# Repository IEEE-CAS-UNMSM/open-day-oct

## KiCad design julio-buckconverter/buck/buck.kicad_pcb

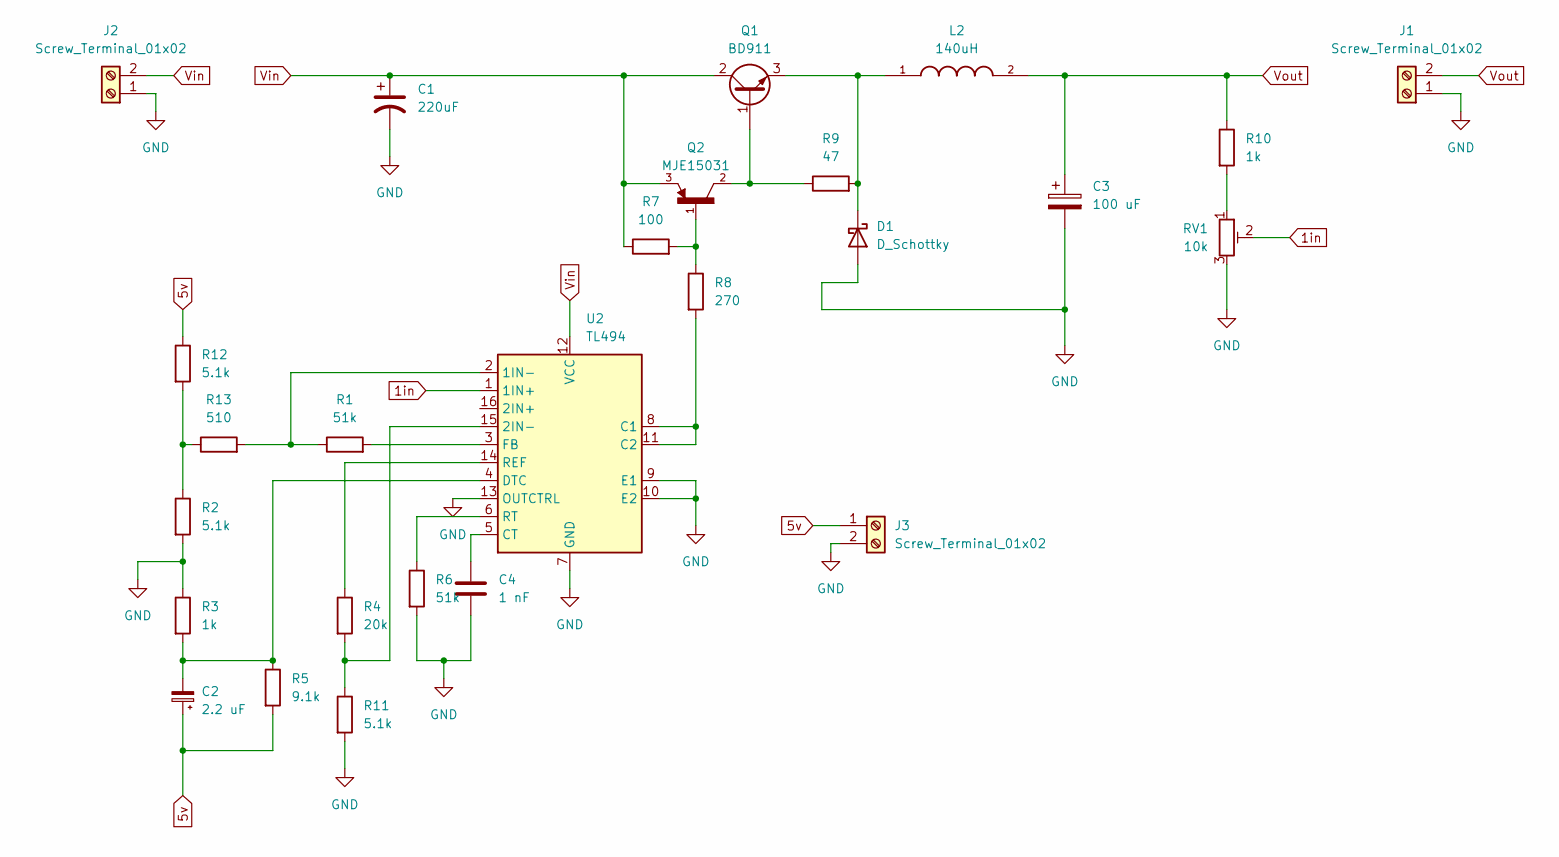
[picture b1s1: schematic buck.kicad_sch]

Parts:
C1: 220uF; CP_Axial_L10.0mm_D4.5mm_P15.00mm_Horizontal
C2: 2.2 uF; CP_Axial_L10.0mm_D4.5mm_P15.00mm_Horizontal
C3: 100 uF; CP_Axial_L10.0mm_D4.5mm_P15.00mm_Horizontal
C4: 1 nF; C_Axial_L3.8mm_D2.6mm_P7.50mm_Horizontal
D1: D_Schottky; D_A-405_P7.62mm_Horizontal
J1, J2, J3: Screw_Terminal_01x02; TerminalBlock_Wuerth_691311400102_P7.62mm
L2: 140uH; IND_HCTI-68-7.7; PARTREV N/A
Q1: BD911; TO-220-3_Vertical
Q2: MJE15031; TO254P1042X498X2993-3
R1: 51k; R_Axial_DIN0207_L6.3mm_D2.5mm_P7.62mm_Horizontal
R2, R12: 5.1k; R_Axial_DIN0207_L6.3mm_D2.5mm_P10.16mm_Horizontal
R3: 1k; R_Axial_DIN0207_L6.3mm_D2.5mm_P7.62mm_Horizontal
R4: 20k; R_Axial_DIN0207_L6.3mm_D2.5mm_P10.16mm_Horizontal
R5: 9.1k; R_Axial_DIN0207_L6.3mm_D2.5mm_P7.62mm_Horizontal
R6: 51k; R_Axial_DIN0207_L6.3mm_D2.5mm_P10.16mm_Horizontal
R7: 100; R_Axial_DIN0207_L6.3mm_D2.5mm_P7.62mm_Horizontal
R8: 270; R_Axial_DIN0207_L6.3mm_D2.5mm_P10.16mm_Horizontal
R9: 47; R_Axial_DIN0207_L6.3mm_D2.5mm_P7.62mm_Horizontal
R10: 1k; R_Axial_DIN0207_L6.3mm_D2.5mm_P10.16mm_Horizontal
R11: 5.1k; R_Axial_DIN0207_L6.3mm_D2.5mm_P7.62mm_Horizontal
R13: 510; R_Axial_DIN0207_L6.3mm_D2.5mm_P7.62mm_Horizontal
RV1: 10k; Potentiometer_ACP_CA9-V10_Vertical
U2: TL494; DIP-16_W7.62mm

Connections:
1in: RV1.2, U2.1 (1IN+)
5v: C2.1, J3.1, R5.2, R12.1
GND: C1.2, C3.2, C4.2, D1.2 (A), J1.1, J2.1, J3.2, R2.2, R3.1, R6.2, R11.2, RV1.3, U2.7 (GND), U2.9 (E1), U2.10 (E2), U2.13 (OUTCTRL)
unnamed: D1.1 (K), L2.1, Q1.3 (E), R9.2
unnamed: Q1.1 (B), Q2.2, R9.1
unnamed: Q2.1, R7.2, R8.1
unnamed: R10.2, RV1.1
unnamed: R2.1, R12.2, R13.1
unnamed: R1.1, R13.2, U2.2 (1IN-)
unnamed: R4.2, R11.1, U2.15 (2IN-)
unnamed: R8.2, U2.8 (C1), U2.11 (C2)
unnamed: C4.1, U2.5 (CT)
unnamed: C2.2, R3.2, R5.1, U2.4 (DTC)
unnamed: R1.2, U2.3 (FB)
unnamed: R4.1, U2.14 (REF)
unnamed: R6.1, U2.6 (RT)
Vin: C1.1, J2.2, Q1.2 (C), Q2.3, R7.1, U2.12 (VCC)
Vout: C3.1, J1.2, L2.2, R10.1

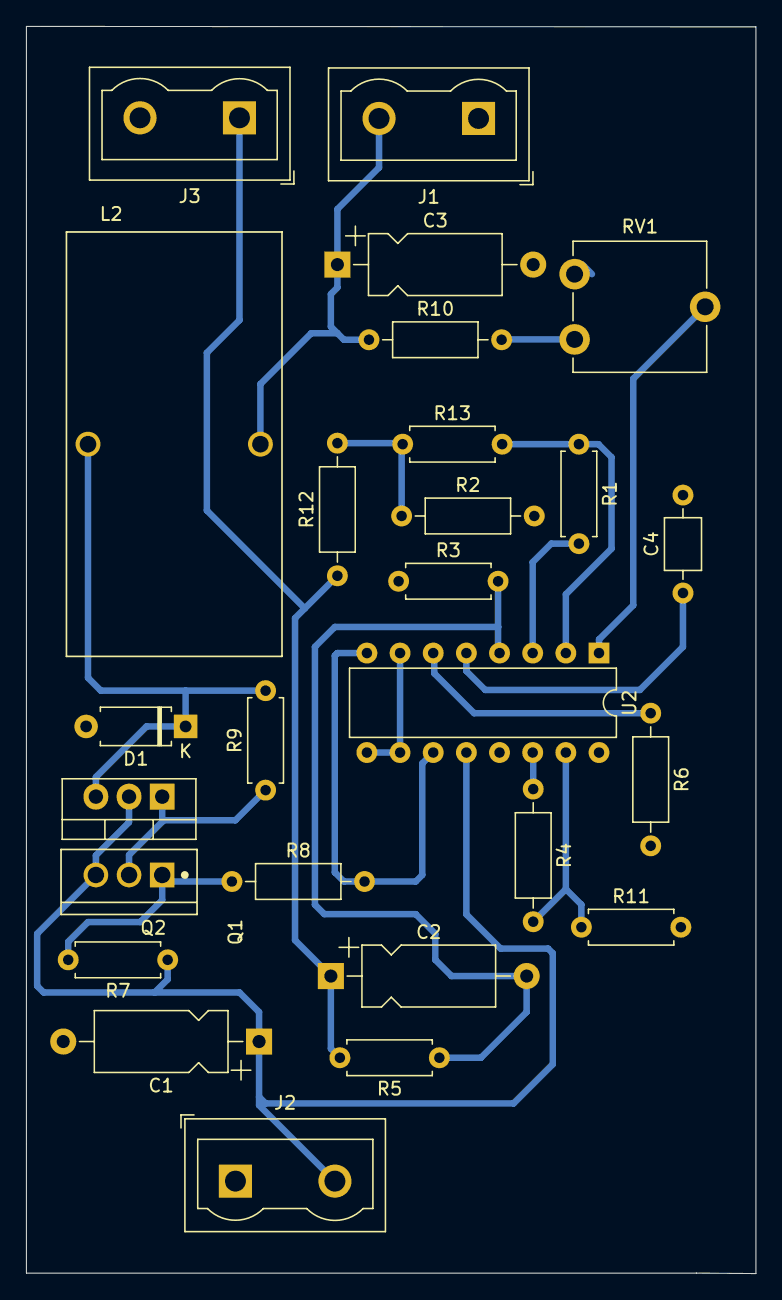
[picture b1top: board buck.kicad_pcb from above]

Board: 2 copper layers, 55.9 x 95.5 mm, 26 parts (0 on the bottom side), 18 nets.

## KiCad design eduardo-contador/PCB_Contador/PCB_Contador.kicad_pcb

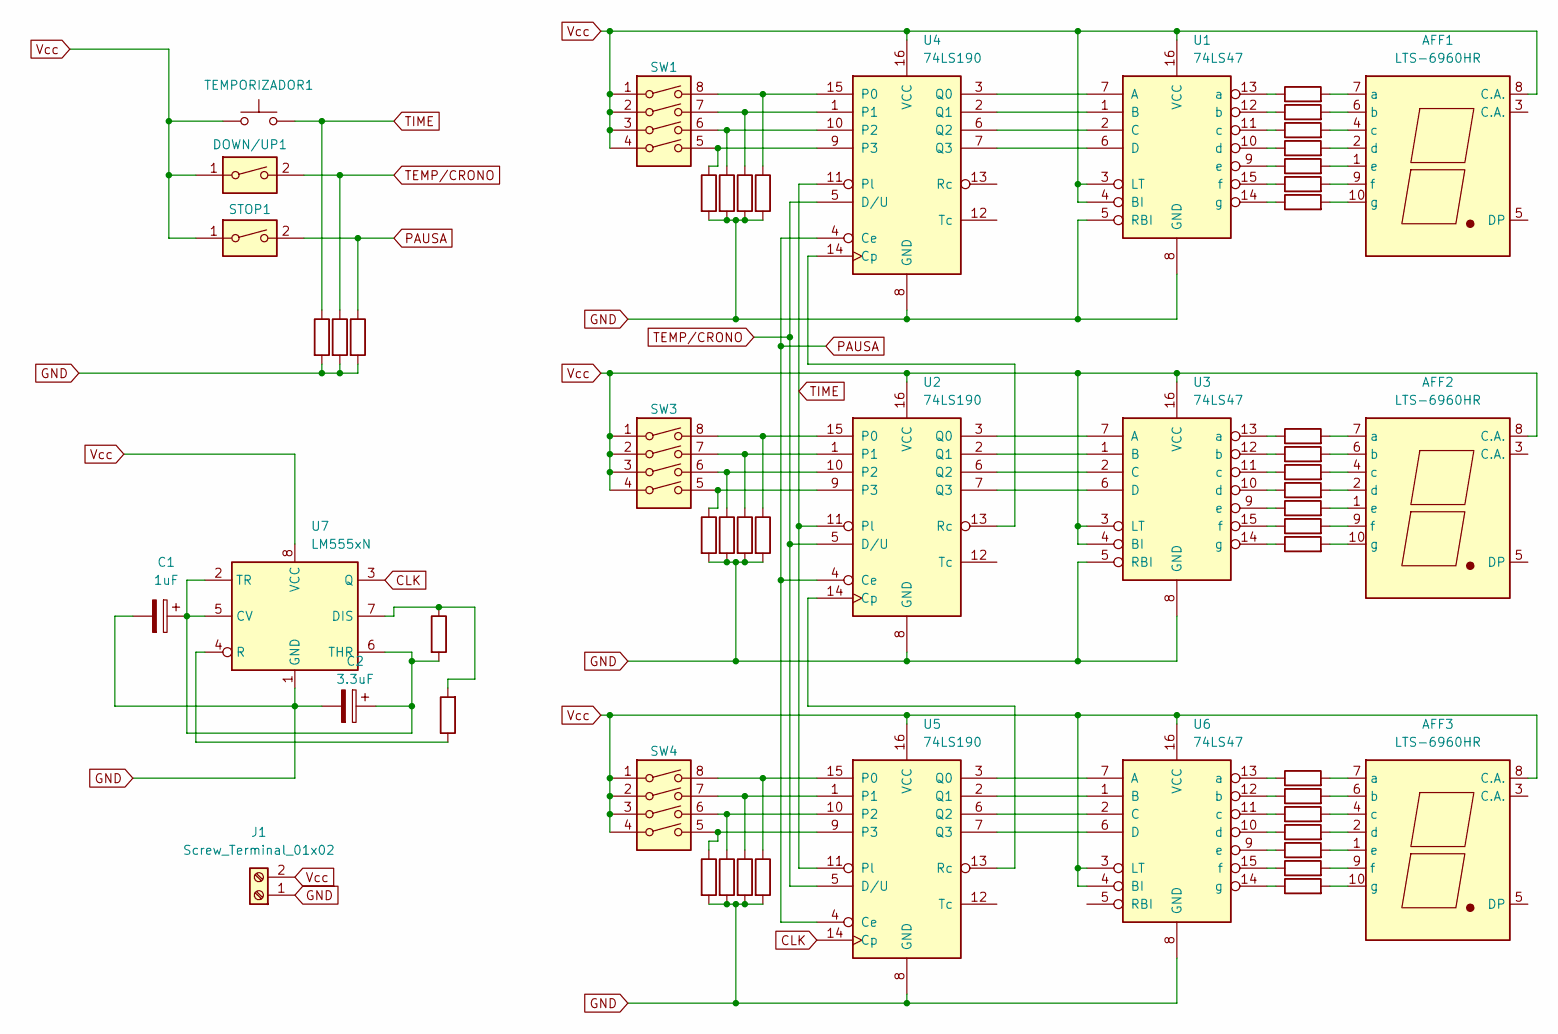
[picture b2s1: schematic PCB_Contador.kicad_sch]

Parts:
AFF1, AFF2, AFF3: LTS-6960HR; 7SegmentLED_LTS6760_LTS6780
C1: 1uF; CP_Radial_D5.0mm_P2.00mm
C2: 3.3uF; CP_Radial_D5.0mm_P2.00mm
DOWN/UP1: SW_DIP_SPSTx01_Slide_6.7x4.1mm_W7.62mm_P2.54mm_LowProfile
J1: Screw_Terminal_01x02; TerminalBlock_Xinya_XY308-2.54-2P_1x02_P2.54mm_Horizontal
R1, R2, R3, R4, R6, R7, R8, R9, R10, R11, R12, R13, R14, R15, R16, R17, R18, R19, R20, R21, R22, R23, R24, R25, R26, R27, R28, R29, R30, R31, R32, R33, R34, R35, R36: R; R_Axial_DIN0207_L6.3mm_D2.5mm_P10.16mm_Horizontal
R5: r=R; R_Axial_DIN0207_L6.3mm_D2.5mm_P10.16mm_Horizontal
R37: 200k; R_Axial_DIN0207_L6.3mm_D2.5mm_P10.16mm_Horizontal
R38: 36k; R_Axial_DIN0207_L6.3mm_D2.5mm_P10.16mm_Horizontal
STOP1: SW_DIP_SPSTx01_Slide_6.7x4.1mm_W7.62mm_P2.54mm_LowProfile
SW1, SW3, SW4: SW_DIP_x04; SW_DIP_SPSTx04_Slide_9.78x12.34mm_W7.62mm_P2.54mm
TEMPORIZADOR1: SW_Push; SW_PUSH_6mm
U1, U3, U6: 74LS47; DIP-16_W7.62mm
U2, U4, U5: 74LS190; DIP-16_W7.62mm
U7: LM555xN; DIP-8_W7.62mm

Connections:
CLK: U5.14 (Cp), U7.3 (Q)
GND: C1.2, C2.2, J1.1, R1.2, R2.2, R3.2, R4.2, R12.2, R13.2, R14.2, R15.2, R23.2, R24.2, R25.2, R26.2, R34.2, R35.2, R36.2, U1.5 (RBI), U1.8 (GND), U2.8 (GND), U3.5 (RBI), U3.8 (GND), U4.8 (GND), U5.8 (GND), U6.8 (GND), U7.1 (GND)
unnamed: AFF1.7 (a), R5.2
unnamed: AFF1.6 (b), R6.2
unnamed: AFF1.4 (c), R7.2
unnamed: AFF1.2 (d), R8.2
unnamed: AFF1.1 (e), R9.2
unnamed: AFF1.9 (f), R10.2
unnamed: AFF1.10 (g), R11.2
unnamed: AFF2.7 (a), R16.2
unnamed: AFF2.6 (b), R17.2
unnamed: AFF2.4 (c), R18.2
unnamed: AFF2.2 (d), R19.2
unnamed: AFF2.1 (e), R20.2
unnamed: AFF2.9 (f), R21.2
unnamed: AFF2.10 (g), R22.2
unnamed: AFF3.7 (a), R27.2
unnamed: AFF3.6 (b), R28.2
unnamed: AFF3.4 (c), R29.2
unnamed: AFF3.2 (d), R30.2
unnamed: AFF3.1 (e), R31.2
unnamed: AFF3.9 (f), R32.2
unnamed: AFF3.10 (g), R33.2
unnamed: U1.7 (A), U4.3 (Q0)
unnamed: U1.1 (B), U4.2 (Q1)
unnamed: U1.2 (C), U4.6 (Q2)
unnamed: U1.6 (D), U4.7 (Q3)
unnamed: R5.1, U1.13 (a)
unnamed: R6.1, U1.12 (b)
unnamed: R7.1, U1.11 (c)
unnamed: R8.1, U1.10 (d)
unnamed: R9.1, U1.9 (e)
unnamed: R10.1, U1.15 (f)
unnamed: R11.1, U1.14 (g)
unnamed: U2.14 (Cp), U5.13 (Rc)
unnamed: R15.1, SW3.8, U2.15 (P0)
unnamed: R14.1, SW3.7, U2.1
unnamed: R13.1, SW3.6, U2.10 (P2)
unnamed: R12.1, SW3.5, U2.9 (P3)
unnamed: U2.3 (Q0), U3.7 (A)
unnamed: U2.2 (Q1), U3.1 (B)
unnamed: U2.6 (Q2), U3.2 (C)
unnamed: U2.7 (Q3), U3.6 (D)
unnamed: U2.13 (Rc), U4.14 (Cp)
unnamed: R16.1, U3.13 (a)
unnamed: R17.1, U3.12 (b)
unnamed: R18.1, U3.11 (c)
unnamed: R19.1, U3.10 (d)
unnamed: R20.1, U3.9 (e)
unnamed: R21.1, U3.15 (f)
unnamed: R22.1, U3.14 (g)
unnamed: R4.1, SW1.8, U4.15 (P0)
unnamed: R3.1, SW1.7, U4.1
unnamed: R2.1, SW1.6, U4.10 (P2)
unnamed: R1.1, SW1.5, U4.9 (P3)
unnamed: R26.1, SW4.8, U5.15 (P0)
unnamed: R25.1, SW4.7, U5.1
unnamed: R24.1, SW4.6, U5.10 (P2)
unnamed: R23.1, SW4.5, U5.9 (P3)
unnamed: U5.3 (Q0), U6.7 (A)
unnamed: U5.2 (Q1), U6.1 (B)
unnamed: U5.6 (Q2), U6.2 (C)
unnamed: U5.7 (Q3), U6.6 (D)
unnamed: R27.1, U6.13 (a)
unnamed: R28.1, U6.12 (b)
unnamed: R29.1, U6.11 (c)
unnamed: R30.1, U6.10 (d)
unnamed: R31.1, U6.9 (e)
unnamed: R32.1, U6.15 (f)
unnamed: R33.1, U6.14 (g)
unnamed: C1.1, C2.1, R37.2, U7.2 (TR), U7.5 (CV), U7.6 (THR)
unnamed: R37.1, R38.2, U7.7 (DIS)
unnamed: R38.1, U7.4 (R)
PAUSA: R36.1, STOP1.2, U2.4 (Ce), U4.4 (Ce), U5.4 (Ce)
TEMP/CRONO: DOWN/UP1.2, R35.1, U2.5 (D/U), U4.5 (D/U), U5.5 (D/U)
TIME: R34.1, TEMPORIZADOR1.2, U2.11 (Pl), U4.11 (Pl), U5.11 (Pl)
Vcc: AFF1.8 (C.A.), AFF2.8 (C.A.), AFF3.8 (C.A.), DOWN/UP1.1, J1.2, STOP1.1, SW1.1, SW1.2, SW1.3, SW1.4, SW3.1, SW3.2, SW3.3, SW3.4, SW4.1, SW4.2, SW4.3, SW4.4, TEMPORIZADOR1.1, U1.3 (LT), U1.4 (BI), U1.16 (VCC), U2.16 (VCC), U3.3 (LT), U3.4 (BI), U3.16 (VCC), U4.16 (VCC), U5.16 (VCC), U6.3 (LT), U6.4 (BI), U6.16 (VCC), U7.8 (VCC)

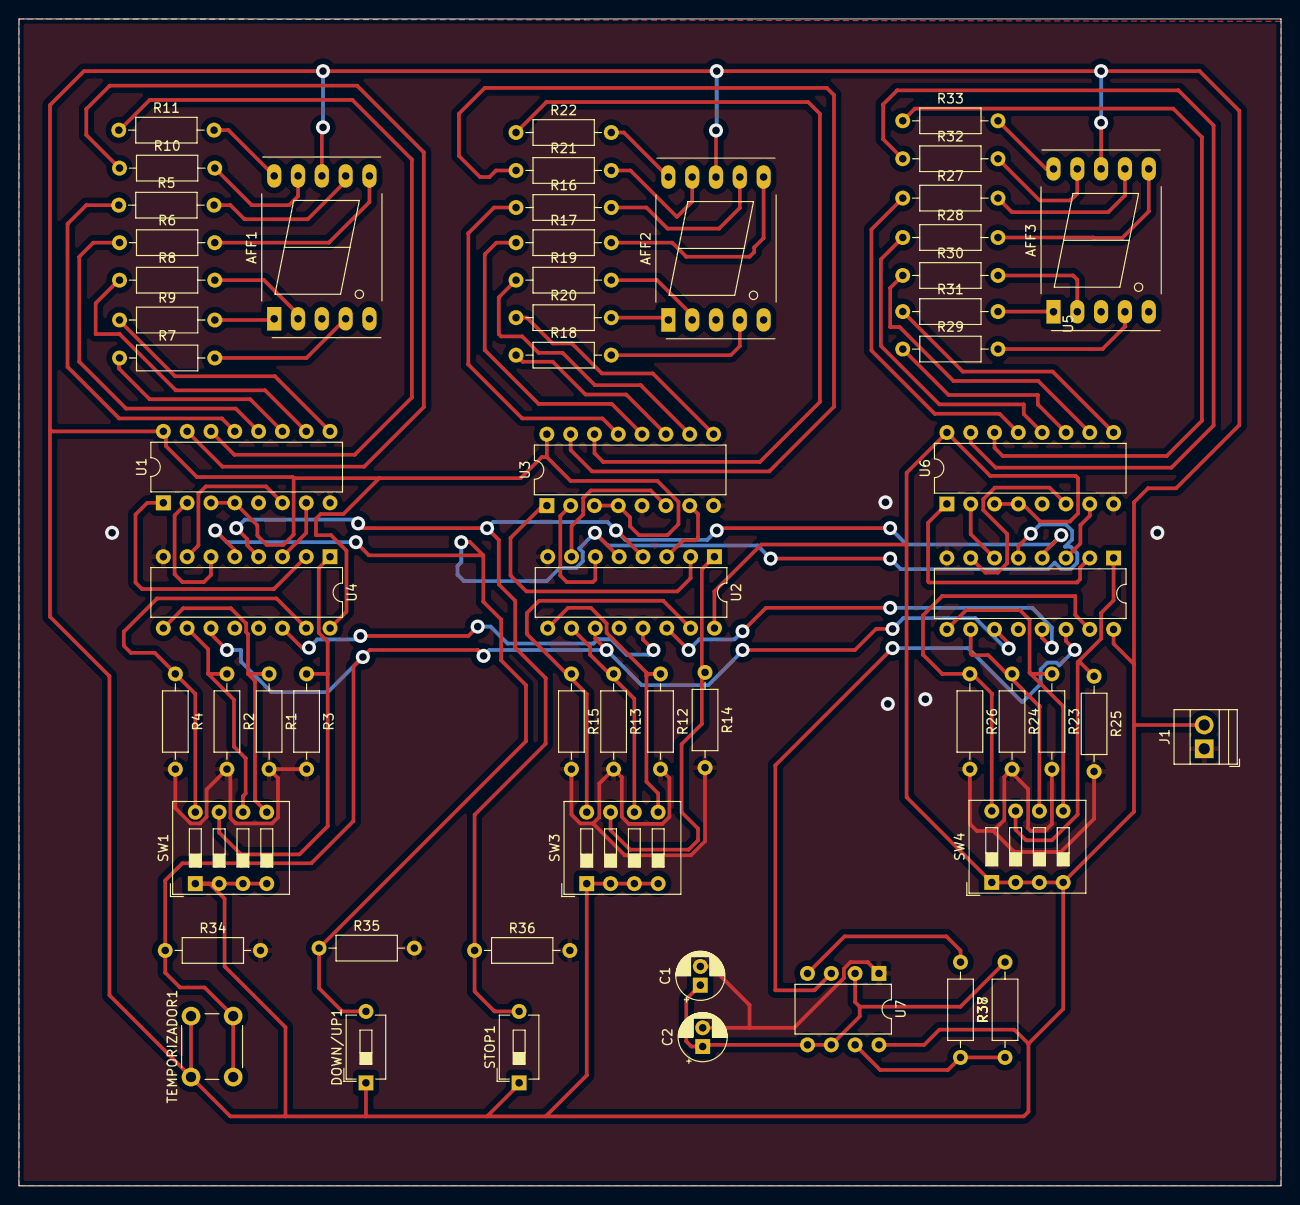
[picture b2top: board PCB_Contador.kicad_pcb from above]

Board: 2 copper layers, 134.6 x 124.5 mm, 57 parts (0 on the bottom side), 77 nets.

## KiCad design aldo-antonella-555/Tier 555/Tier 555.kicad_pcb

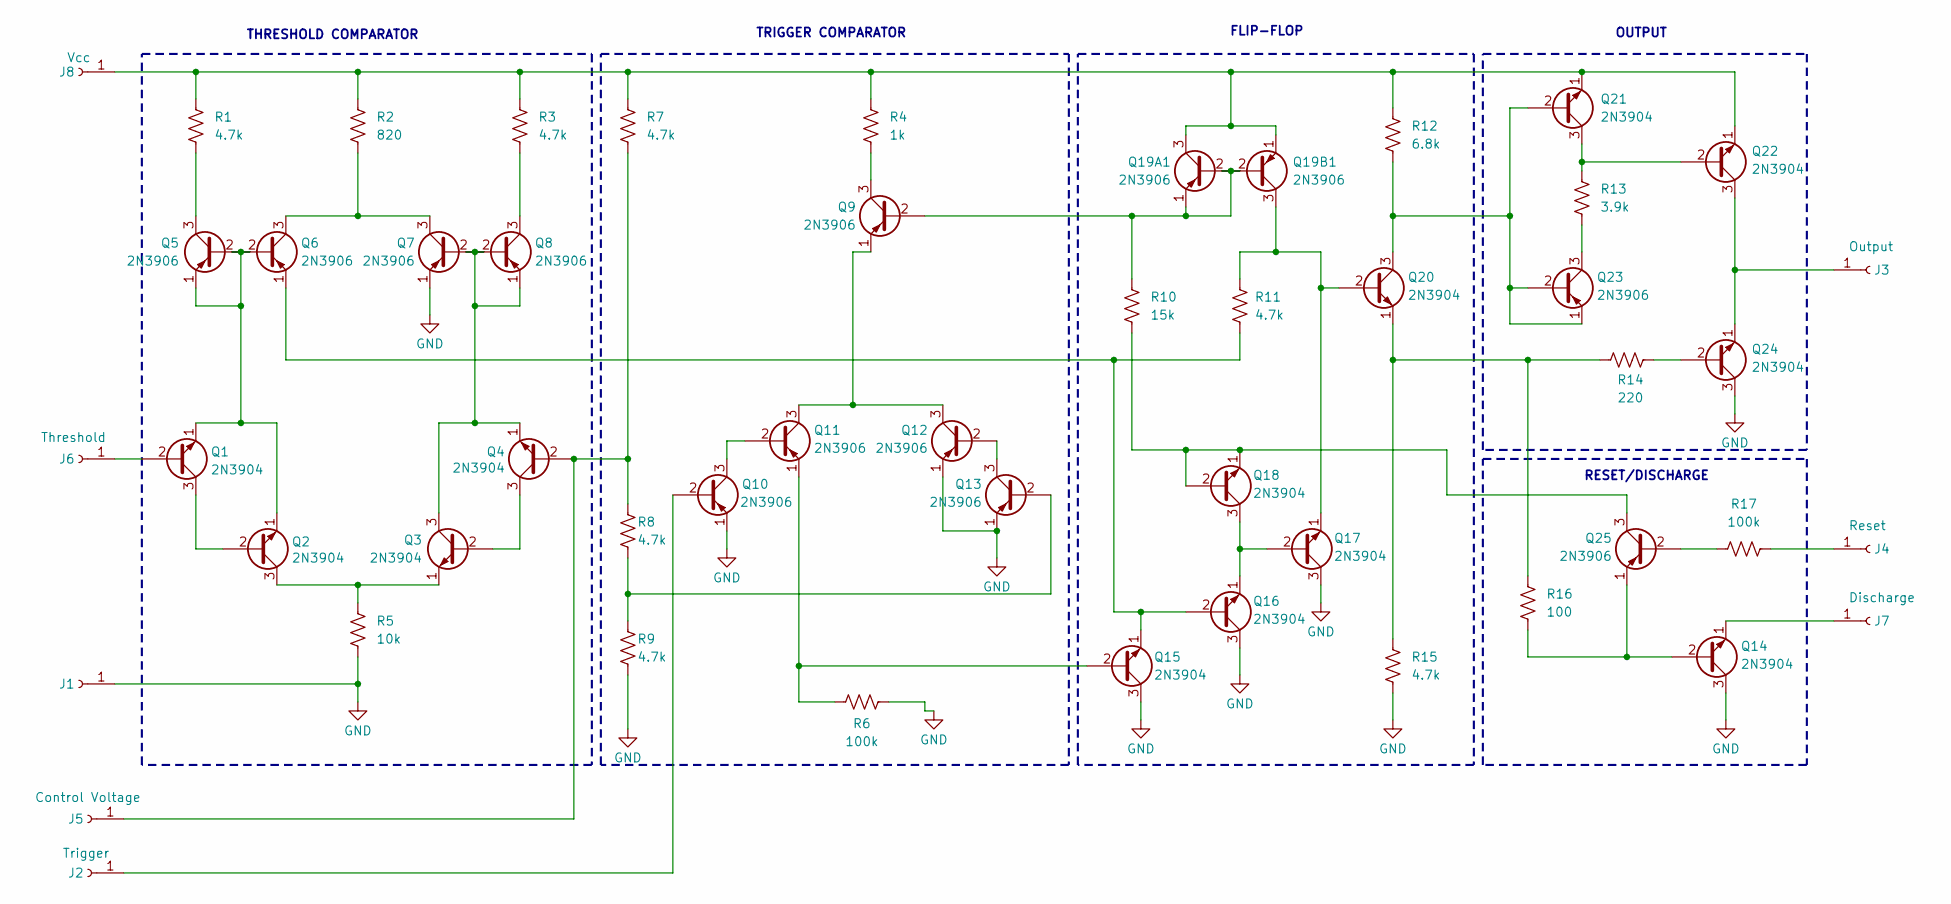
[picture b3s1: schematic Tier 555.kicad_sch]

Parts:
J1: GND; PinHeader_1x01_P2.54mm_Vertical
J2: Trigger; PinHeader_1x01_P2.54mm_Vertical
J3: Output; PinHeader_1x01_P2.54mm_Vertical
J4: Reset; PinHeader_1x01_P2.54mm_Vertical
J5: Control Voltage; PinHeader_1x01_P2.54mm_Vertical
J6: Threshold; PinHeader_1x01_P2.54mm_Vertical
J7: Discharge; PinHeader_1x01_P2.54mm_Vertical
J8: Vcc; PinHeader_1x01_P2.54mm_Vertical
Q1, Q2, Q3, Q4, Q14, Q15, Q16, Q17, Q18, Q20, Q21, Q22, Q24: 2N3904; TO-92_Inline
Q5, Q6, Q7, Q8, Q9, Q10, Q11, Q12, Q13, Q19A1, Q19B1, Q23, Q25: 2N3906; TO-92_Inline
R1, R3, R7, R8, R9, R11, R15: 4.7k; R_Axial_DIN0207_L6.3mm_D2.5mm_P10.16mm_Horizontal
R2: 820; R_Axial_DIN0207_L6.3mm_D2.5mm_P10.16mm_Horizontal
R4: 1k; R_Axial_DIN0207_L6.3mm_D2.5mm_P10.16mm_Horizontal
R5: 10k; R_Axial_DIN0207_L6.3mm_D2.5mm_P10.16mm_Horizontal
R6, R17: 100k; R_Axial_DIN0207_L6.3mm_D2.5mm_P10.16mm_Horizontal
R10: 15k; R_Axial_DIN0207_L6.3mm_D2.5mm_P10.16mm_Horizontal
R12: 6.8k; R_Axial_DIN0207_L6.3mm_D2.5mm_P10.16mm_Horizontal
R13: 3.9k; R_Axial_DIN0207_L6.3mm_D2.5mm_P10.16mm_Horizontal
R14: 220; R_Axial_DIN0207_L6.3mm_D2.5mm_P10.16mm_Horizontal
R16: 100; R_Axial_DIN0207_L6.3mm_D2.5mm_P10.16mm_Horizontal

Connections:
GND: J1.1, Q7.1 (E), Q10.1 (E), Q12.1 (E), Q13.1 (E), Q14.3 (C), Q15.3 (C), Q16.3 (C), Q17.3 (C), Q24.3 (C), R5.2, R6.1, R9.2, R15.2
unnamed: J2.1, Q10.2 (B)
unnamed: J3.1, Q22.3 (C), Q24.1 (E)
unnamed: J4.1, R17.2
unnamed: J5.1, Q4.2 (B), R7.2, R8.1
unnamed: J6.1, Q1.2 (B)
unnamed: J7.1, Q14.1 (E)
unnamed: J8.1, Q19A1.3 (C), Q19B1.1 (E), Q21.1 (E), Q22.1 (E), R1.1, R2.1, R3.1, R4.1, R7.1, R12.1
unnamed: Q1.3 (C), Q2.2 (B)
unnamed: Q1.1 (E), Q2.1 (E), Q5.1 (E), Q5.2 (B), Q6.2 (B)
unnamed: Q2.3 (C), Q3.1 (E), R5.1
unnamed: Q3.2 (B), Q4.3 (C)
unnamed: Q3.3 (C), Q4.1 (E), Q7.2 (B), Q8.1 (E), Q8.2 (B)
unnamed: Q5.3 (C), R1.2
unnamed: Q6.3 (C), Q7.3 (C), R2.2
unnamed: Q8.3 (C), R3.2
unnamed: Q9.3 (C), R4.2
unnamed: Q10.3 (C), Q11.2 (B)
unnamed: Q9.1 (E), Q11.3 (C), Q12.3 (C)
unnamed: Q11.1 (E), Q15.2 (B), R6.2
unnamed: Q12.2 (B), Q13.3 (C)
unnamed: Q13.2 (B), R8.2, R9.1
unnamed: Q14.2 (B), Q25.1 (E), R16.2
unnamed: Q6.1 (E), Q15.1 (E), Q16.2 (B), R11.2
unnamed: Q16.1 (E), Q17.2 (B), Q18.3 (C)
unnamed: Q17.1 (E), Q19B1.3 (C), Q20.2 (B), R11.1
unnamed: Q18.1 (E), Q18.2 (B), Q25.3 (C), R10.2
unnamed: Q9.2 (B), Q19A1.1 (E), Q19A1.2 (B), Q19B1.2 (B), R10.1
unnamed: Q20.3 (C), Q21.2 (B), Q23.1 (E), Q23.2 (B), R12.2
unnamed: Q20.1 (E), R14.1, R15.1, R16.1
unnamed: Q21.3 (C), Q22.2 (B), R13.1
unnamed: Q23.3 (C), R13.2
unnamed: Q24.2 (B), R14.2
unnamed: Q25.2 (B), R17.1

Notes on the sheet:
OUTPUT
RESET/DISCHARGE
FLIP-FLOP
THRESHOLD COMPARATOR
TRIGGER COMPARATOR

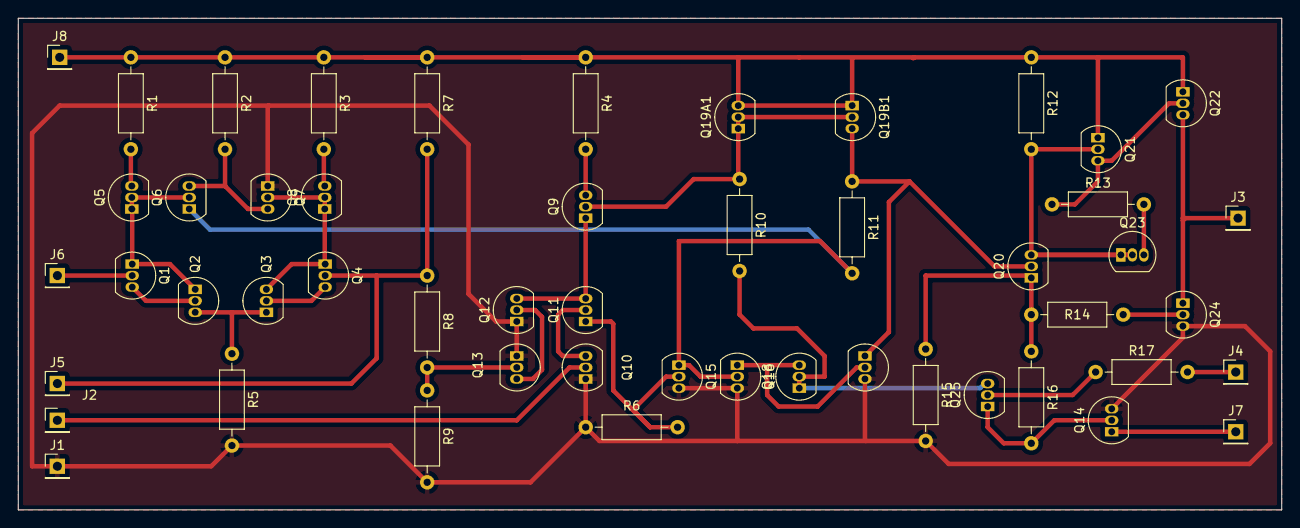
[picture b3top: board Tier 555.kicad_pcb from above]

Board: 2 copper layers, 139.7 x 54.4 mm, 51 parts (0 on the bottom side), 34 nets.

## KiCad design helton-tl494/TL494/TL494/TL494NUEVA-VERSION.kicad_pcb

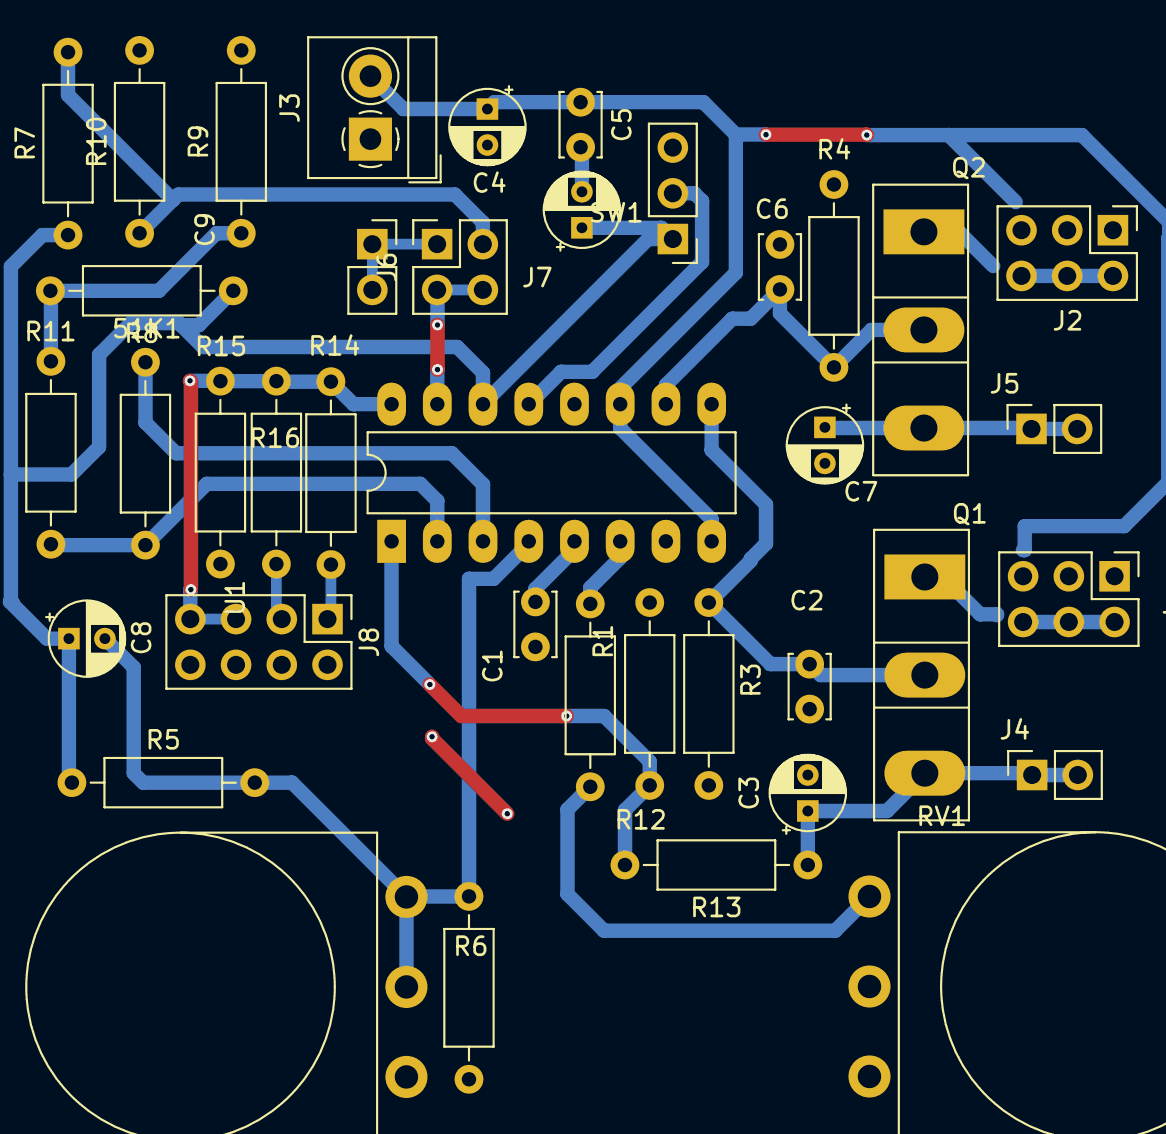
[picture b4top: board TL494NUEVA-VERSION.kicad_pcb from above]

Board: 2 copper layers, 39 parts (0 on the bottom side), 22 nets.

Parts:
51K1: 510; R_Axial_DIN0207_L6.3mm_D2.5mm_P10.16mm_Horizontal
C1: 1uF; C_Disc_D3.4mm_W2.1mm_P2.50mm
C2, C6: 15pF; C_Disc_D3.4mm_W2.1mm_P2.50mm
C3, C7: 10uF; CP_Radial_D4.0mm_P2.00mm
C4, C8, C9: 100uF; CP_Radial_D4.0mm_P2.00mm
C5: 10nF; C_Disc_D3.4mm_W2.1mm_P2.50mm
J1, J2: Jumper E1; PinHeader_2x03_P2.54mm_Vertical
J3: +-; TerminalBlock_4Ucon_1x02_P3.50mm_Horizontal
J4, J5, J7: Vout1; PinSocket_1x02_P2.54mm_Vertical
J6: Conn_02x02_Odd_Even; PinSocket_2x02_P2.54mm_Vertical
J8: Conn_02x04_Odd_Even; PinHeader_2x04_P2.54mm_Vertical
Q1, Q2: NMOS; TO-247-3_Vertical
R1: 2k; R_Axial_DIN0207_L6.3mm_D2.5mm_P10.16mm_Horizontal
R3, R4: 68; R_Axial_DIN0207_L6.3mm_D2.5mm_P10.16mm_Horizontal
R5: 100k; R_Axial_DIN0207_L6.3mm_D2.5mm_P10.16mm_Horizontal
R6, R10: 1k; R_Axial_DIN0207_L6.3mm_D2.5mm_P10.16mm_Horizontal
R7: 4k; R_Axial_DIN0207_L6.3mm_D2.5mm_P10.16mm_Horizontal
R8, R9: 5.1k; R_Axial_DIN0207_L6.3mm_D2.5mm_P10.16mm_Horizontal
R11: 510; R_Axial_DIN0207_L6.3mm_D2.5mm_P10.16mm_Horizontal
R12, R14, R15: 10k; R_Axial_DIN0207_L6.3mm_D2.5mm_P10.16mm_Horizontal
R13: 50k; R_Axial_DIN0207_L6.3mm_D2.5mm_P10.16mm_Horizontal
R16: 30k; R_Axial_DIN0207_L6.3mm_D2.5mm_P10.16mm_Horizontal
RV1: 20k; Potentiometer_Omeg_PC16BU_Vertical
RV2: 100k; Potentiometer_Omeg_PC16BU_Vertical
SW1: CTRL; PinHeader_1x03_P2.54mm_Vertical
U1: TL494; DIP-16_W7.62mm_LongPads

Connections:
1IN+: R12.1, R13.2, U1.1 (1IN+)
1IN-: 51K1.1, R11.1, U1.2 (1IN-)
2IN+: J8.5, J8.7, R14.1, R15.2, R16.2, U1.16 (2IN+)
2IN-: J6.2, J6.4, U1.15 (2IN-)
CT: C1.1, U1.5 (CT)
CTRL: SW1.2 (B), U1.13 (OUTCTRL)
DTC: C8.2, R5.2, R6.2, RV2.1, RV2.2, U1.4 (DTC)
E1: C2.2, Q1.2 (G), R3.1, U1.9 (E1)
E2: C6.2, Q2.2 (G), R4.1, U1.10 (E2)
FB: 51K1.2, U1.3 (FB)
GNDREF: C1.2, C2.1, C3.2, C4.2, C5.2, C6.1, C7.2, C9.2, J3.1, J8.8, R3.2, R4.2, R6.1, R9.2, R10.2, R12.2, R15.1, RV1.1, RV1.2, RV2.3, SW1.3 (C), U1.7 (GND)
unnamed: C7.1, J5.1, J5.2, Q2.3 (S)
unnamed: J6.1, J7.1, J7.2
unnamed: J6.3, R7.2, R10.1
unnamed: J8.1, R14.2
unnamed: J8.3, R16.1
unnamed: R1.2, RV1.3
unnamed: R8.2, R9.1, R11.2
OUTV1: C3.1, J4.1, J4.2, Q1.3 (S), R13.1
RT: R1.1, U1.6 (RT)
VCC: C4.1, C5.1, J3.2, U1.8 (C1), U1.11 (C2), U1.12 (VCC)
VREF: C8.1, C9.1, R5.1, R7.1, R8.1, SW1.1 (A), U1.14 (REF)

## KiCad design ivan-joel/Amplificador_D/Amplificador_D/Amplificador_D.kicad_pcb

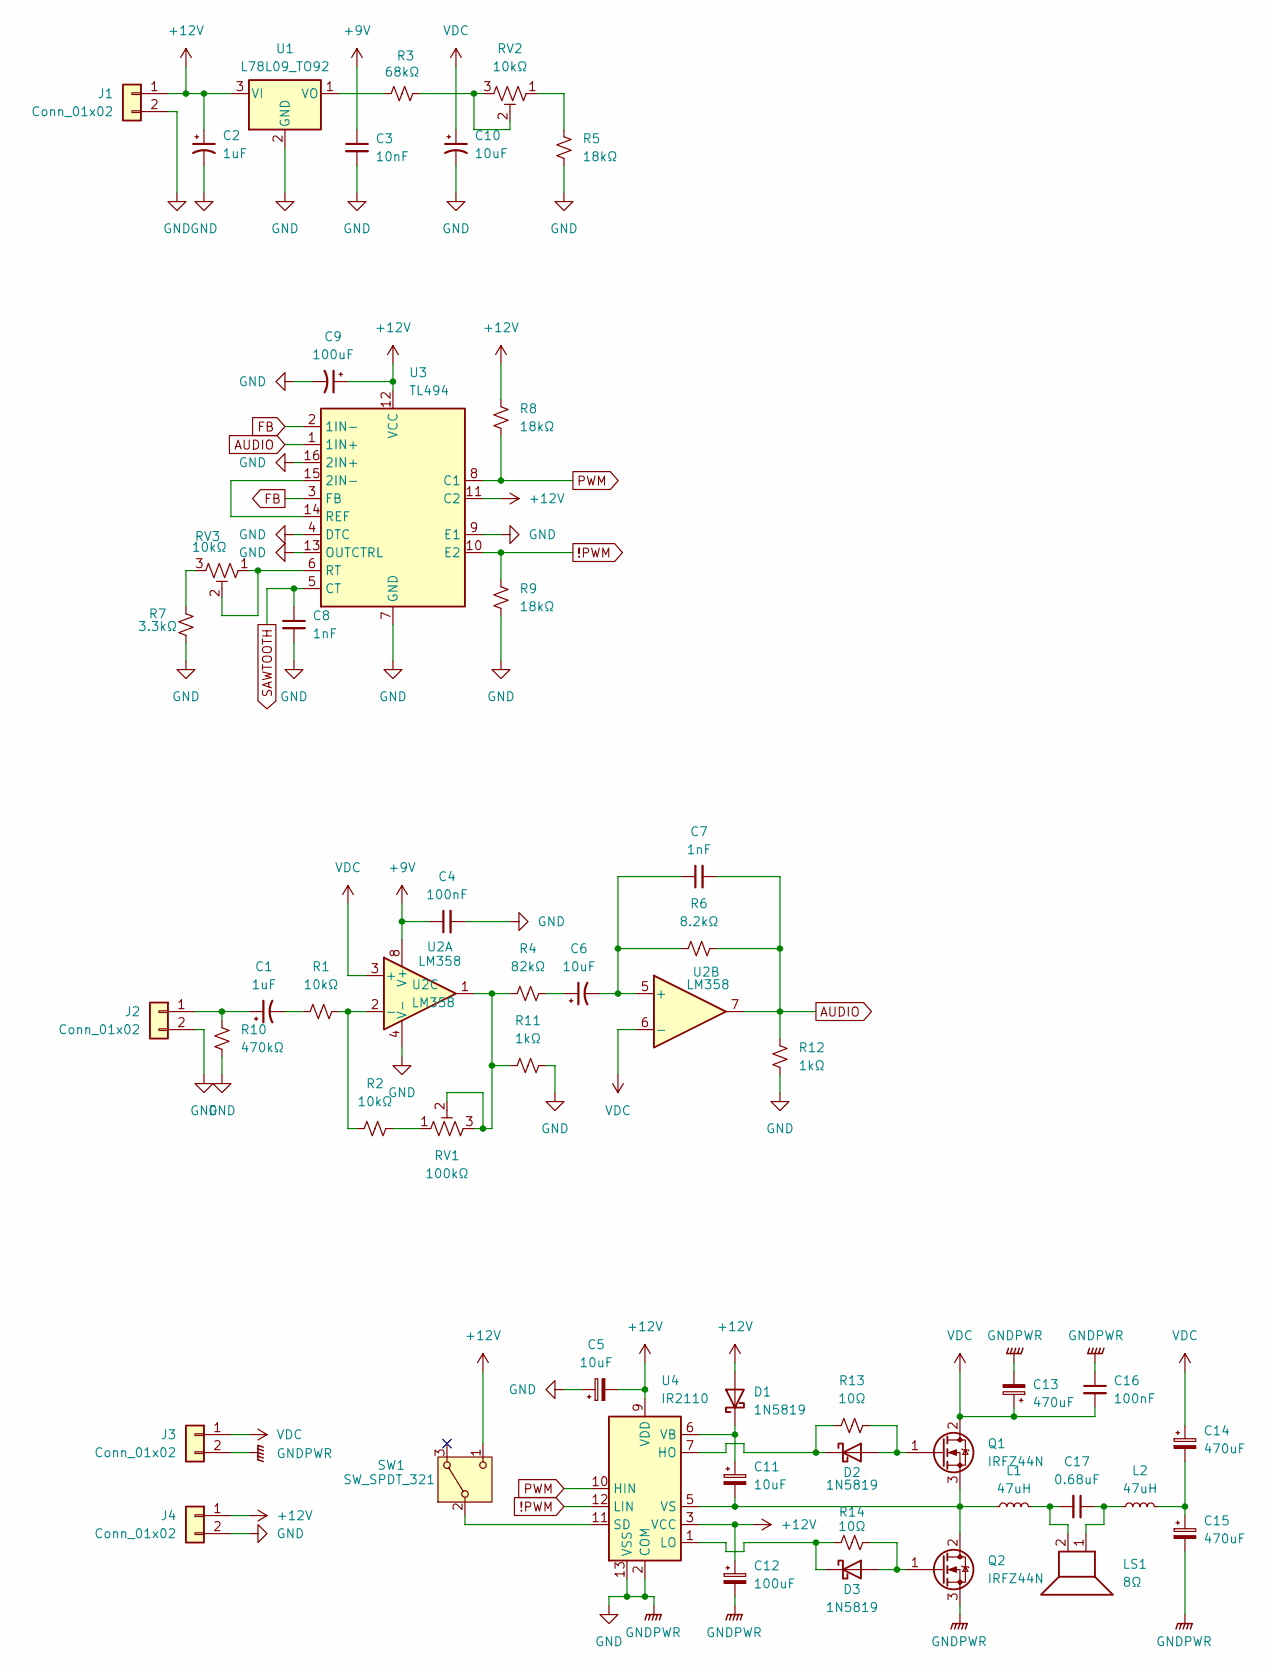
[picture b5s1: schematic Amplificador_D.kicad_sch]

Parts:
C1, C2: 1uF; CP_Radial_D5.0mm_P2.00mm
C3: 10nF; C_Disc_D3.8mm_W2.6mm_P2.50mm
C4: 100nF; C_Disc_D5.0mm_W2.5mm_P5.00mm
C5, C6, C10, C11: 10uF; CP_Radial_D5.0mm_P2.00mm
C7, C8: 1nF; C_Disc_D3.8mm_W2.6mm_P2.50mm
C9: 100uF; CP_Radial_D6.3mm_P2.50mm
C12: 100uF; CP_Radial_D8.0mm_P2.50mm
C13, C14, C15: 470uF; CP_Radial_D10.0mm_P5.00mm
C16: 100nF; C_Disc_D3.8mm_W2.6mm_P2.50mm
C17: 0.68uF; C_Rect_L7.0mm_W3.5mm_P5.00mm
D1, D2, D3: 1N5819; D_DO-41_SOD81_P10.16mm_Horizontal
J1: Conn_01x02; BarrelJack_GCT_DCJ200-10-A_Horizontal
J2, J3, J4: Conn_01x02; JST_XH_B2B-XH-A_1x02_P2.50mm_Vertical
L1, L2: 47uH; L_Radial_D12.5mm_P7.00mm_Fastron_09HCP
LS1: 8Ω; Molex_KK-396_A-41791-0002_1x02_P3.96mm_Vertical
Q1, Q2: IRFZ44N; TO-220-3_Vertical
R1, R2: 10kΩ; R_Axial_DIN0204_L3.6mm_D1.6mm_P7.62mm_Horizontal
R3: 68kΩ; R_Axial_DIN0204_L3.6mm_D1.6mm_P7.62mm_Horizontal
R4: 82kΩ; R_Axial_DIN0204_L3.6mm_D1.6mm_P7.62mm_Horizontal
R5, R8, R9: 18kΩ; R_Axial_DIN0204_L3.6mm_D1.6mm_P7.62mm_Horizontal
R6: 8.2kΩ; R_Axial_DIN0204_L3.6mm_D1.6mm_P7.62mm_Horizontal
R7: 3.3kΩ; R_Axial_DIN0204_L3.6mm_D1.6mm_P7.62mm_Horizontal
R10: 470kΩ; R_Axial_DIN0204_L3.6mm_D1.6mm_P7.62mm_Horizontal
R11, R12: 1kΩ; R_Axial_DIN0204_L3.6mm_D1.6mm_P7.62mm_Horizontal
R13, R14: 10Ω; R_Axial_DIN0204_L3.6mm_D1.6mm_P7.62mm_Horizontal
RV1: 100kΩ; Potentiometer_Bourns_3296W_Vertical
RV2, RV3: 10kΩ; Potentiometer_Bourns_3296W_Vertical
SW1: SW_SPDT_321; SW_NKK_GW12LJP
U1: L78L09_TO92; TO-92_Inline_Wide
U2: LM358; DIP-8_W7.62mm
U3: TL494; DIP-16_W7.62mm
U4: IR2110; DIP-14_W7.62mm

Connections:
!PWM: R9.1, U3.10 (E2), U4.12 (LIN)
+9V: C3.1, C4.1, U2.8 (V+)
+12V: C2.1, C5.2, C9.1, C12.1, D1.2 (A), J1.1, J4.1, R8.1, SW1.1 (C), U1.3 (VI), U3.11 (C2), U3.12 (VCC), U4.3 (VCC), U4.9 (VDD)
AUDIO: C7.2, R6.2, R12.2, U2.7, U3.1 (1IN+)
FB: U3.2 (1IN-), U3.3 (FB)
GND: C2.2, C3.2, C4.2, C5.1, C8.2, C9.2, C10.2, C12.2, C13.2, C15.2, C16.1, J1.2, J2.2, J3.2, J4.2, Q2.3 (S), R5.2, R7.2, R9.2, R10.2, R11.2, R12.1, U1.2 (GND), U2.4 (V-), U3.4 (DTC), U3.7 (GND), U3.9 (E1), U3.13 (OUTCTRL), U3.16 (2IN+), U4.2 (COM), U4.13 (VSS)
unnamed: C1.2, R1.1
unnamed: C6.1, R4.2
unnamed: C14.2, C15.1, L2.2
unnamed: C17.1, L2.1, LS1.1
unnamed: C17.2, L1.2, LS1.2
unnamed: C11.1, D1.1 (K), U4.6 (VB)
unnamed: D2.2 (A), Q1.1 (G), R13.2
unnamed: D2.1 (K), R13.1, U4.7 (HO)
unnamed: D3.2 (A), Q2.1 (G), R14.2
unnamed: D3.1 (K), R14.1, U4.1 (LO)
unnamed: C1.1, J2.1, R10.1
unnamed: C11.2, L1.1, Q1.3 (S), Q2.2 (D), U4.5 (VS)
unnamed: R2.2, RV1.1
unnamed: R3.2, RV2.2, RV2.3
unnamed: R5.1, RV2.1
unnamed: R7.1, RV3.3
unnamed: R4.1, R11.1, RV1.2, RV1.3, U2.1
unnamed: SW1.2 (B), U4.11 (SD)
unnamed: R3.1, U1.1 (VO)
unnamed: R1.2, R2.1, U2.2 (-)
unnamed: C6.2, C7.1, R6.1, U2.5 (+)
unnamed: U3.14 (REF), U3.15 (2IN-)
unnamed: RV3.1, RV3.2, U3.6 (RT)
PWM: R8.2, U3.8 (C1), U4.10 (HIN)
SAWTOOTH: C8.1, U3.5 (CT)
VDC: C10.1, C13.1, C14.1, C16.2, J3.1, Q1.2 (D), U2.3 (+), U2.6 (-)

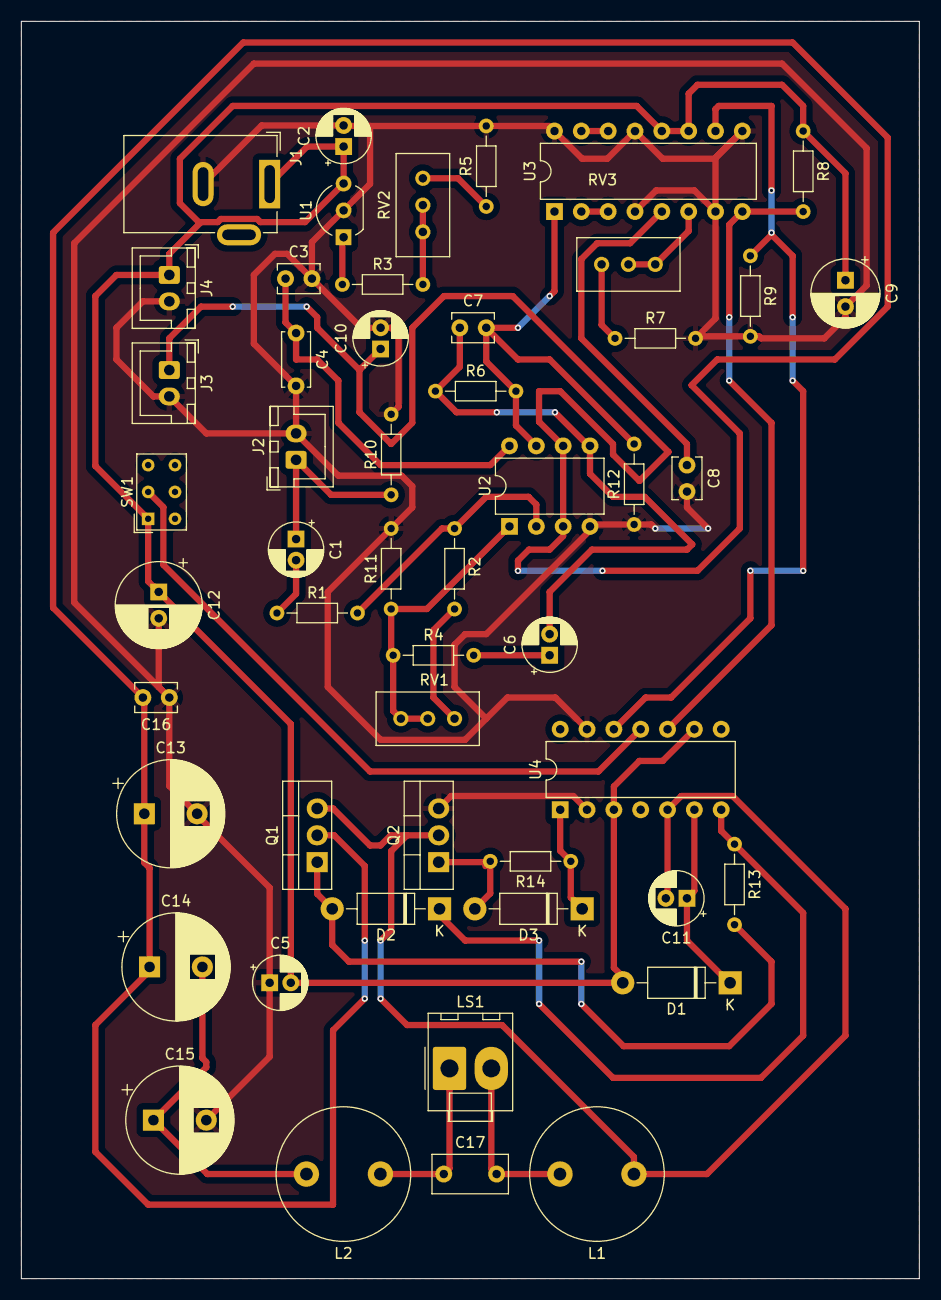
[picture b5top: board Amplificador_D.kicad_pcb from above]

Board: 2 copper layers, 85.0 x 119.0 mm, 51 parts (0 on the bottom side), 32 nets.
